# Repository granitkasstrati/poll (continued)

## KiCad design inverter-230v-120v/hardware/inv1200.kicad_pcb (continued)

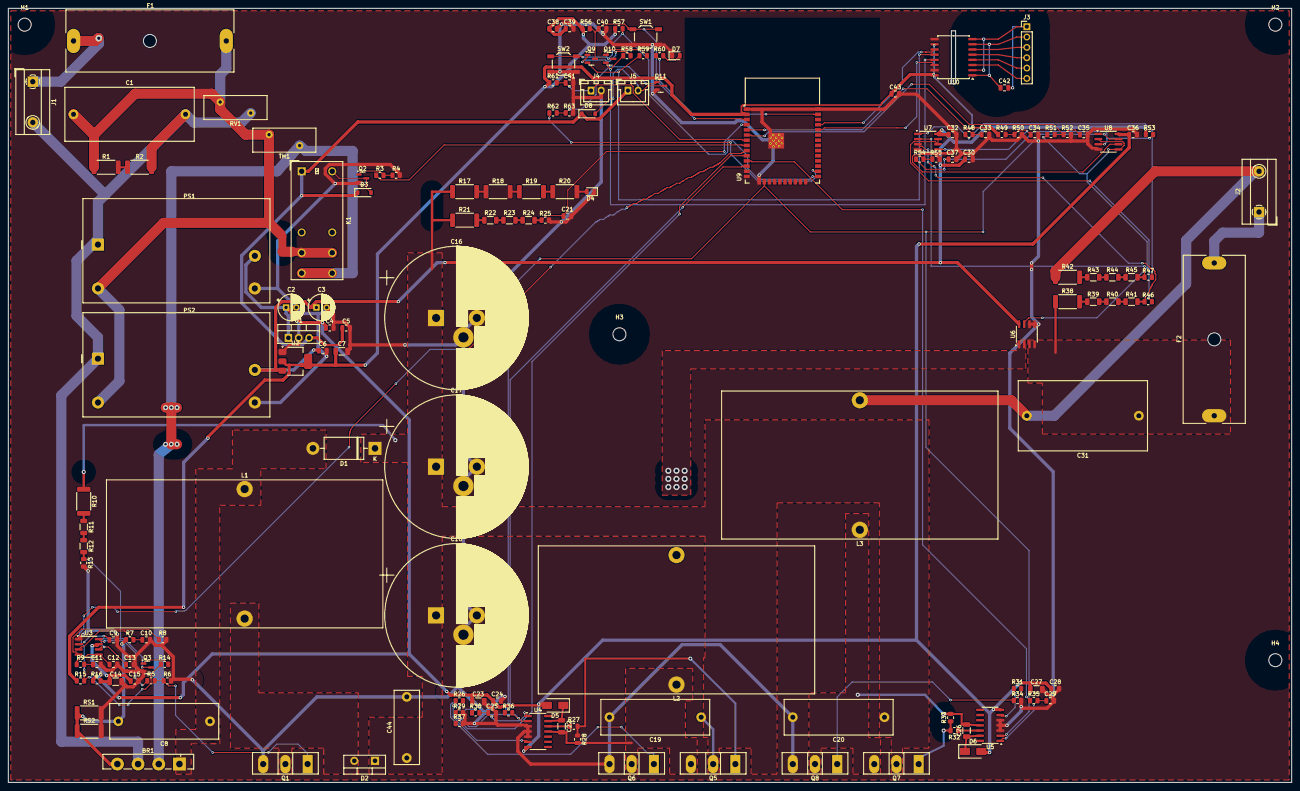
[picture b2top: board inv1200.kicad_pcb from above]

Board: 2 copper layers, 315.0 x 190.0 mm, 159 parts (0 on the bottom side), 96 nets.

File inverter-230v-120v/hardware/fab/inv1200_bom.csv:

Qty,References,Value,Footprint,MPN / suggestion,Notes
1,BR1,GBU15J,Diode_Bridge_Vishay_GBU,Vishay GBU15J or Diodes GBU1506 (15 A 600 V) - on heatsink,
1,C1,1uF X2 275VAC,C_Rect_L31.5mm_W13.0mm_P27.50mm_MKS4,KEMET R46KR410000M1M / WIMA MKP X2,
1,C2,47uF 25V,CP_Radial_D6.3mm_P2.50mm,,
1,C3,100uF 10V,CP_Radial_D6.3mm_P2.50mm,,
1,C4,330nF,C_0805_2012Metric,,
15,C5 C12 C15 C21 C24 C28 C30 C32 C34 C36 C37 C39 C41 C42 C43,100nF,C_0805_2012Metric,,
2,C6 C38,10uF,C_0805_2012Metric,,
1,C7,22uF,C_1206_3216Metric,,
1,C8,1uF 630VDC,C_Rect_L26.5mm_W8.5mm_P22.50mm_MKS4,WIMA MKP4 1uF 630VDC,PFC input HF cap
3,C9 C13 C35,1nF,C_0805_2012Metric,,tune w/ TI calculator
3,C10 C25 C29,100pF,C_0805_2012Metric,,
1,C11,2.2uF,C_0805_2012Metric,,
3,C14 C23 C27,10uF 25V,C_1206_3216Metric,,
3,C16 C17 C18,390uF 450V,CP_Radial_D35.0mm_P10.00mm_3pin_SnapIn,Nichicon LGU2W391MELB / Rubycon 450MXK390 (35x45),
2,C19 C20,1uF 630VDC,C_Rect_L26.5mm_W8.5mm_P22.50mm_MKS4,WIMA MKP4 1uF 630V,leg A decoupling; leg B decoupling
2,C22 C26,1uF 50V,C_1206_3216Metric,,bootstrap
1,C31,3.3uF X2 275VAC,C_Rect_L31.5mm_W17.0mm_P27.50mm_MKS4,KEMET R46 3.3uF X2 / WIMA MKP X2,
1,C33,10nF,C_0805_2012Metric,,
1,C40,1uF,C_0805_2012Metric,,
1,C44,100nF 630VDC,C_Rect_L18.0mm_W6.0mm_P15.00mm_FKS3_FKP3,WIMA FKP3/MKP 100nF 630V,"PFC D2-Q1 HF loop cap, place at D2/Q1"
1,D1,1N5408,D_DO-201AD_P15.24mm_Horizontal,,Inrush bypass around L1/D2
1,D2,C6D10065A,TO-220-2_Vertical,Wolfspeed C6D10065A SiC 650 V 10 A - on heatsink,
2,D3 D8,1N4148W,D_SOD-123,,
1,D4,RED BUS LIVE,LED_0805_2012Metric,,lit while bus > ~30 V
2,D5 D6,ES1J,D_SMA,,bootstrap 600 V fast
1,D7,GREEN STATUS,LED_0805_2012Metric,,
1,F1,T10A 250V,Fuseholder_Cylinder-6.3x32mm_Schurter_0031-8002_Horizontal_Open,Schurter 0031.8002 holder + 6.3x32 T10A ceramic,
1,F2,T12.5A 250V,Fuseholder_Cylinder-6.3x32mm_Schurter_0031-8002_Horizontal_Open,Schurter 0031.8002 holder + 6.3x32 T12.5A,
4,H1 H2 H3 H4,M3,MountingHole_3.2mm_M3,,
1,J1,AC IN 230V,TerminalBlock_MetzConnect_Type067_RT01902HDWC_1x02_P10.00mm_Horizontal,Metz RT01902HDWC 10 mm pitch,"Feed from IEC inlet filter e.g. Schaffner FN9260/FN9264-10 (10 A). PE goes inlet->chassis->outlet, not via PCB"
1,J2,AC OUT 120V,TerminalBlock_MetzConnect_Type067_RT01902HDWC_1x02_P10.00mm_Horizontal,Metz RT01902HDWC 10 mm pitch,NOT isolated from mains - neither pin is neutral/earth
1,J3,PROG (ISOLATED),PinHeader_1x06_P2.54mm_Vertical,,"1 GND, 2 3V3, 3 to adapter RX, 4 RTS, 5 DTR, 6 from adapter TX (order matches U10 pins)"
1,J4,HEATSINK NTC,JST_XH_B2B-XH-A_1x02_P2.50mm_Vertical,"10k B3950 NTC glued to heatsink, insulated",
1,J5,FAN 12V,JST_XH_B2B-XH-A_1x02_P2.50mm_Vertical,,
1,K1,G2RL-1-E 12VDC,Relay_SPDT_Omron_G2RL-1-E,Omron G2RL-1-E DC12 (16 A),
1,L1,450uH 15A,L_Toroid_Vertical_L67.6mm_W36.1mm_P31.80mm_Vishay_TJ9,"2x Magnetics 0077439A7 Kool Mu 60u stacked, ~70 T 1.6 mm (or custom)",
2,L2 L3,150uH 20A,L_Toroid_Vertical_L67.6mm_W36.1mm_P31.80mm_Vishay_TJ9,Kool Mu 0077439A7 ~45 T 1.8 mm (Isat >= 20 A),
1,PS1,IRM-10-15,Converter_ACDC_MeanWell_IRM-10-xx_THT,Mean Well IRM-10-15,
1,PS2,IRM-05-5,Converter_ACDC_MeanWell_IRM-05-xx_THT,Mean Well IRM-05-5,
1,Q1,IPW65R045C7,TO-247-3_Vertical,Infineon IPW65R045C7 - on heatsink,
4,Q2 Q3 Q9 Q10,MMBT3904,SOT-23,,pulls VSENSE low = PFC off
4,Q5 Q6 Q7 Q8,C3M0060065D,TO-247-3_Vertical,Wolfspeed C3M0060065D SiC - on heatsink,
1,Q11,AO3400A,SOT-23,,
2,R1 R2,470k,R_2512_6332Metric,,X-cap discharge
6,R3 R36 R48 R53 R55 R60,1k,R_0805_2012Metric,,0.60 V = -19 A; 4.40 V = +19 A; MCU enable; LM393 can override low
16,R4 R6 R15 R28 R29 R33 R34 R37 R49 R50 R51 R56 R57 R58 R59 R61,10k,R_0805_2012Metric,,PFC off by default; bridge off by default; with 10k NTC on heatsink
1,R5,4R7,R_0805_2012Metric,,
1,R7,220R,R_0805_2012Metric,,
1,R8,33k2,R_0805_2012Metric,,"~65 kHz, check datasheet eq."
2,R9 R25,22k,R_0805_2012Metric,,2.19 V @ 400 V; tune w/ TI calculator
1,R10,1M2,R_2512_6332Metric,,
2,R11 R12,1M2,R_1206_3216Metric,,
1,R13,45k3,R_0805_2012Metric,,0.1%; sets 402 V bus
1,R14,4k7,R_0805_2012Metric,,
5,R16 R26 R27 R31 R32,10R,R_0805_2012Metric,,
4,R17 R18 R19 R20,27k 1W,R_2512_6332Metric,,bleeder
3,R21 R38 R42,1M,R_2512_6332Metric,,
9,R22 R23 R24 R39 R40 R41 R43 R44 R45,1M,R_1206_3216Metric,,
3,R30 R35 R62,100R,R_0805_2012Metric,,
2,R46 R47,28k 0.1%,R_0805_2012Metric,,
1,R52,20k,R_0805_2012Metric,,
1,R54,6k34,R_0805_2012Metric,,
1,R63,100k,R_0805_2012Metric,,
1,RS1,40m 2W,R_2512_6332Metric,Vishay WSL2512R0400 (or Bourns CRA2512),PFC shunt (2 in parallel = 20 mOhm)
1,RS2,40m 2W,R_2512_6332Metric,Vishay WSL2512R0400,
1,RV1,275VAC,RV_Disc_D15.5mm_W5.9mm_P7.5mm,TDK S14K275,
1,SW1,RESET,SW_SPST_TL3342,,
1,SW2,BOOT,SW_SPST_TL3342,,
1,TH1,5R 8A,RV_Disc_D15.5mm_W5.9mm_P7.5mm,"TDK B57237S0509M000 (S237, 5 ohm, 8 A)",
1,U1,L7812,TO-220-3_Vertical,ST L7812CV,
1,U2,AMS1117-3.3,SOT-223-3_TabPin2,,
1,U3,UCC28180,SOIC-8_3.9x4.9mm_P1.27mm,TI UCC28180DR,
2,U4 U5,IR21844S,SOIC-14_3.9x8.7mm_P1.27mm,Infineon IR21844STRPBF,DT tied to VSS = minimum (~0.4 us) dead time; HV pins isolated on one side
1,U6,ACS724LLCTR-20AB,SOIC-8_3.9x4.9mm_P1.27mm,Allegro ACS724LLCTR-20AB-T,pin 6 = BW_SEL tied GND
1,U7,TLV9062IDR,SOIC-8_3.9x4.9mm_P1.27mm,TI TLV9062IDR,
1,U8,LM393,SOIC-8_3.9x4.9mm_P1.27mm,TI LM393DR,
1,U9,ESP32-WROOM-32E-N4,ESP32-WROOM-32D,Espressif ESP32-WROOM-32E-N4,
1,U10,Si8641ED-B-IS,SOIC-16W_7.5x10.3mm_P1.27mm,"Skyworks Si8641ED-B-IS (5 kVrms, default-high outputs)",

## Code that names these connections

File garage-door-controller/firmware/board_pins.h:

/*
 * gdc1 rev A - board pin map (ESP32-S3-WROOM-1-N8R2)
 * Mirrors hardware/gen/design.py; if you change one, change the other.
 */
#pragma once

#include "driver/gpio.h"
#include "hal/adc_types.h"

/* --- door position inputs (opto-isolated, ACTIVE LOW: reed closed = 0) ------ */
#define PIN_IN_CLOSED       GPIO_NUM_16     /* reed at fully-closed position */
#define PIN_IN_OPEN         GPIO_NUM_17     /* reed at fully-open position */
#define PIN_IN_AUX          GPIO_NUM_18     /* spare: pedestrian door, wall-button sense, ... */

/* --- outputs ---------------------------------------------------------------- */
/* RELAY_CMD is AC-coupled (C20/R23, tau ~0.7-1 s): drive a 300-500 ms HIGH pulse,
 * then LOW. Holding it HIGH does NOT hold the relay: it drops out after <=1.6 s. */
#define PIN_RELAY_CMD       GPIO_NUM_7
#define PIN_BUZZER          GPIO_NUM_10     /* self-drive buzzer via AO3400A, active high */
#define PIN_WARN_OUT        GPIO_NUM_15     /* J4 low-side switch (VIN), active high, <=300 mA */
#define PIN_WARN_LED        GPIO_NUM_12     /* red LED, active high */
#define PIN_RGB_DIN         GPIO_NUM_13     /* WS2812B data (RMT), VDD ~4.3 V */

/* --- user interface ---------------------------------------------------------- */
#define PIN_USER_BTN        GPIO_NUM_14     /* active low, 10k pull-up */
#define PIN_BOOT_BTN        GPIO_NUM_0      /* strap; usable as an input after boot */

/* --- I2C: BME280 (0x76) + Qwiic J7 (e.g. VL53L1X 0x29) ------------------------- */
#define PIN_I2C_SDA         GPIO_NUM_8
#define PIN_I2C_SCL         GPIO_NUM_9
#define BME280_I2C_ADDR     0x76

/* --- analog (ADC1 only: ADC2 is unusable while Wi-Fi runs) -------------------- */
#define PIN_VIN_SENSE       GPIO_NUM_4      /* ADC1_CH3, VIN / 15.7 (R7 100k, R8 6.8k) */
#define ADC_CH_VIN_SENSE    ADC_CHANNEL_3
#define VIN_SENSE_RATIO     ((100.0f + 6.8f) / 6.8f)
#define PIN_EXP_ADC         GPIO_NUM_2      /* ADC1_CH1 on J6 pin 2 (CT clamp burden) */
#define ADC_CH_EXP          ADC_CHANNEL_1

/* --- expansion header J6 --------------------------------------------------- */
#define PIN_EXP_IO38        GPIO_NUM_38
#define PIN_EXP_IO39        GPIO_NUM_39
#define PIN_EXP_IO40        GPIO_NUM_40     /* suggested UART1 TX */
#define PIN_EXP_IO41        GPIO_NUM_41     /* suggested UART1 RX */

/* USB D-/D+ = GPIO19/GPIO20 (USB-Serial-JTAG), UART0 = GPIO43/44 on J5 (ESP-Prog). */

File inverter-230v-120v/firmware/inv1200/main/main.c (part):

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static const char *TAG = "inv1200";

/* ---- pins (see hardware/gen/design.py, U9 map) ---------------------------- */
#define PIN_PWM_A     25
#define PIN_PWM_B     26
#define PIN_INV_EN    27   /* high = allow bridge (through R36 1k)            */
#define PIN_INV_SD_N  13   /* read-back, MCPWM fault input (active low)       */
#define PIN_RELAY_EN  32   /* high = bypass NTC                               */
#define PIN_PFC_DIS   33   /* high/floating = PFC off (Q3 pulls VSENSE low)   */
#define PIN_FAN       4
#define PIN_LED       23
/* ADC1: IO36 VBUS, IO39 VOUT, IO34 IOUT, IO35 heatsink NTC */
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    ESP_ERROR_CHECK(mcpwm_new_timer(&tc, &s_timer));

    mcpwm_gpio_fault_config_t fc = {
        .group_id = 0, .gpio_num = PIN_INV_SD_N, .flags.active_level = 0, .flags.pull_up = false,
    };
    mcpwm_fault_handle_t fault;
    ESP_ERROR_CHECK(mcpwm_new_gpio_fault(&fc, &fault));

    const int pins[2] = {PIN_PWM_A, PIN_PWM_B};
    mcpwm_cmpr_handle_t *cmps[2] = {&s_cmp_a, &s_cmp_b};
    for (int k = 0; k < 2; k++) {
        mcpwm_oper_handle_t op;
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static void gpio_init(void)
{
    gpio_config_t out = {
        .pin_bit_mask = (1ULL << PIN_INV_EN) | (1ULL << PIN_RELAY_EN) | (1ULL << PIN_FAN) | (1ULL << PIN_LED),
        .mode = GPIO_MODE_OUTPUT,
    };
    ESP_ERROR_CHECK(gpio_config(&out));
    gpio_set_level(PIN_INV_EN, 0);
    gpio_set_level(PIN_RELAY_EN, 0);
    /* PFC_DIS: leave as input (R15 pull-up keeps PFC OFF) until we want it on */
    gpio_reset_pin(PIN_PFC_DIS);
    gpio_set_direction(PIN_PFC_DIS, GPIO_MODE_INPUT);
}

static void pfc_enable(bool on)
{
    if (on) {
        gpio_set_direction(PIN_PFC_DIS, GPIO_MODE_OUTPUT);
        gpio_set_level(PIN_PFC_DIS, 0);            /* Q3 off -> UCC28180 runs   */
    } else {
        gpio_set_direction(PIN_PFC_DIS, GPIO_MODE_INPUT);  /* pull-up -> off    */
    }
}

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
static void trip(const char *why)
{
    gpio_set_level(PIN_INV_EN, 0);
    s_m_q15 = 0;
    pfc_enable(false);
    ESP_LOGE(TAG, "TRIP: %s", why);
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        vTaskDelay(pdMS_TO_TICKS(50));
    }
    ESP_LOGI(TAG, "precharged %.0f V -> relay", last);
    gpio_set_level(PIN_RELAY_EN, 1);
    vTaskDelay(pdMS_TO_TICKS(100));

    /* 2. PFC boost to ~400 V */
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    /* 3. inverter soft start: ramp modulation over 0.5 s */
    gpio_set_level(PIN_FAN, 1);
    s_m_q15 = 0;
    gpio_set_level(PIN_INV_EN, 1);
    vTaskDelay(pdMS_TO_TICKS(2));
    /* INV_SD_N idles low (R37) so the one-shot brake latched at boot: clear it now */
    if (gpio_get_level(PIN_INV_SD_N) == 0) trip("INV_SD_N stuck low (comparator trip?)");
    for (int k = 0; k < 2; k++) ESP_ERROR_CHECK(mcpwm_operator_recover_from_fault(s_ops[k]));
    float m = 0.0f, m_ff;
    const TickType_t period = pdMS_TO_TICKS(20);           /* one output cycle */
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        float vb = vbus();
        if (vb > 440.0f) trip("bus over-voltage");
        if (vb < 330.0f) trip("bus under-voltage");
        if (gpio_get_level(PIN_INV_SD_N) == 0 && gpio_get_level(PIN_INV_EN)) trip("hardware over-current");

        /* coarse RMS: ~1 kHz sampling inside this task */
        for (int k = 0; k < 20; k++) {
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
